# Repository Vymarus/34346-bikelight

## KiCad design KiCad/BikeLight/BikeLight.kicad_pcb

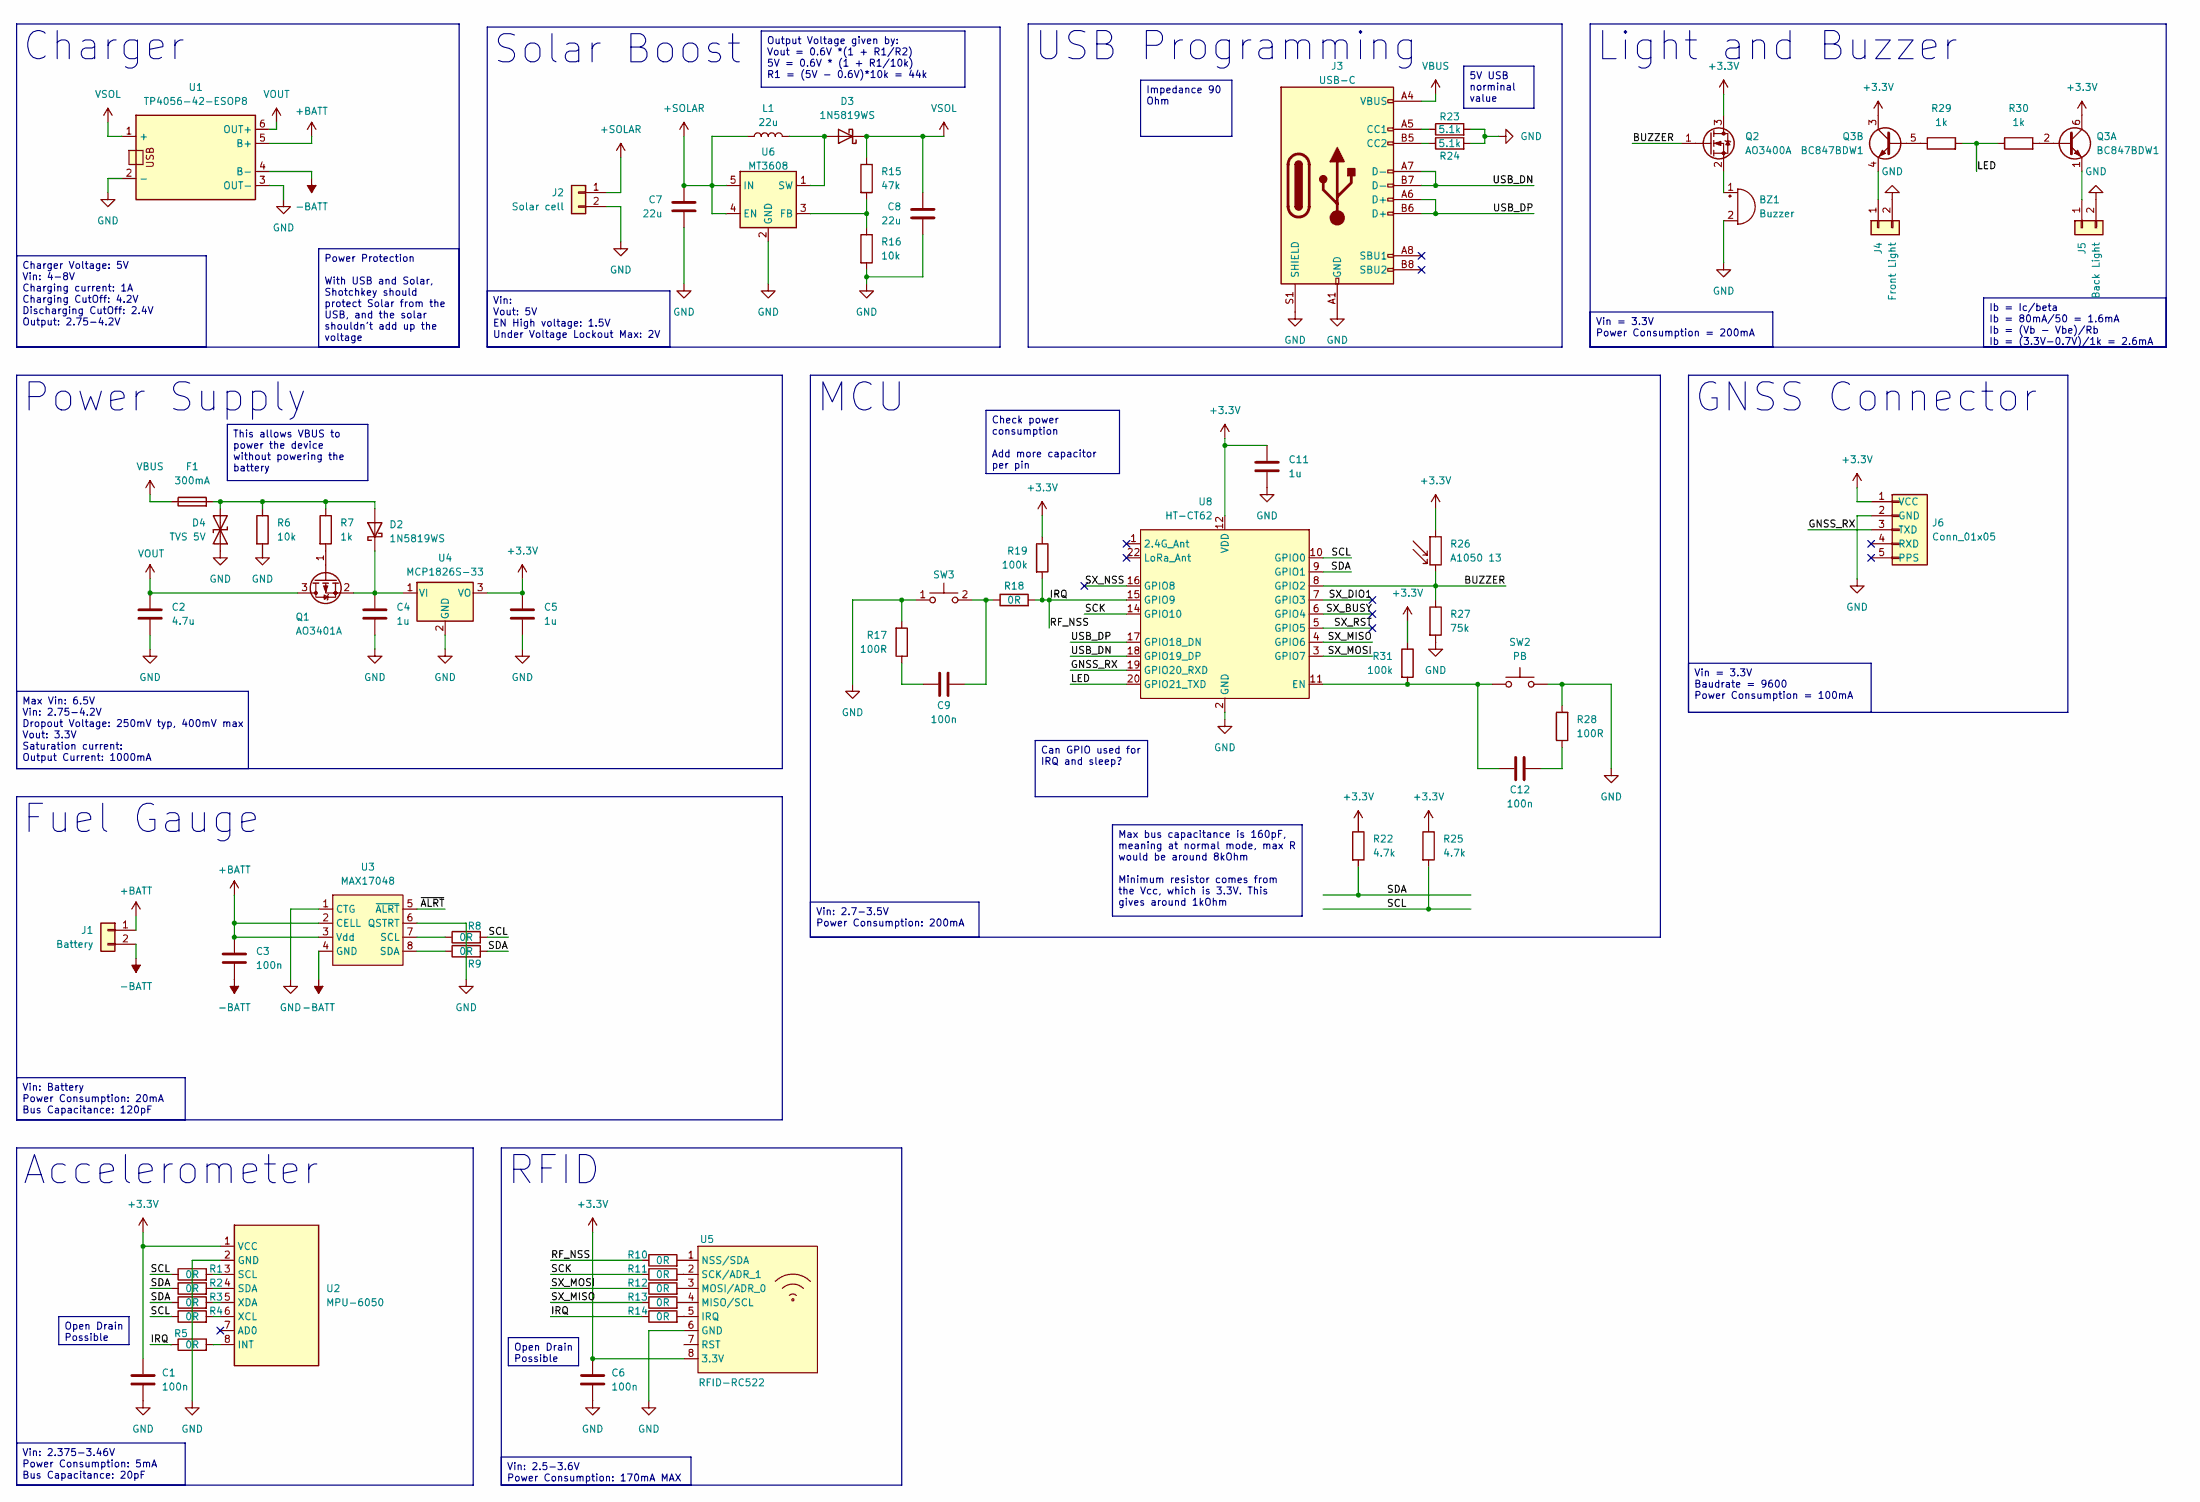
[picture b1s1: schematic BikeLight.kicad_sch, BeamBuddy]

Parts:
BZ1: TMB12A03; Buzzer_12x9.5RM7.6; MPN TMB12A03
C1, C3, C6, C9, C12: 100n_0603_TCC0603X7R104K500CT; C_0603_1608Metric; Tolerance 10%; Rating 50V; MPN TCC0603X7R104K500CT
C2: 4.7u_0805_CL21A475KAQNNNE; C_0805_2012Metric; Rating 25V; Tolerance 10%; MPN CL21A475KAQNNNE
C4: 1u_0603_CL10A105KA8NNNC; C_0603_1608Metric; MPN CL10A105KA8NNNC
C5, C11: 1u_0603_UMK107BJ105KA-T; C_0603_1608Metric; MPN UMK107BJ105KA-T
C7, C8: 22u_0805_CL21A226MAQNNNE; C_0805_2012Metric; Rating 10V; Tolerance 20%; MPN CL21A226MAQNNNE
D2, D3: 1N5819WS; D_SOD-323; MPN 1N5819WS
D4: SMAJ5.0CA/TR13_NONAME; D_SMA; MPN SMAJ5.0CA/TR13
F1: MF-MSMF010-2; Fuse_1812_4532Metric; MPN MF-MSMF010-2
J1, J2, J4, J5: Conn-01x02_P2.5mm_S2B-XH-A-BK(LF)(SN); JST_XH_S2B-XH-A_1x02_P2.50mm_Horizontal; MPN S2B-XH-A-BK(LF)(SN)
J3: GT-USB-7051A; USB-C-SMD_GT-USB-7051A; MPN GT-USB-7051A
J6: Conn_01x05; PinHeader_1x05_P2.54mm_Horizontal; LCSC C492413
L1: 22u_620mA_1210_CBC3225T220KR; L_1210_3225Metric; Rating 620mA; MPN CBC3225T220KR
Q1: AO3401A; SOT-23; MPN AO3401A
Q2: AO3400A; SOT-23; MPN AO3400A
Q3: BC847BDW1; SOT-363_SC-70-6
R1, R2, R3, R4, R5, R8, R9, R10, R11, R12, R13, R14, R18: 0R_0603_0603WAF0000T5E; R_0603_1608Metric; MPN 0603WAF0000T5E
R6, R16: 10k_0603_RC0603JR-0710KL; R_0603_1608Metric; Tolerance 1%; MPN RC0603JR-0710KL
R7, R29, R30: 1k_0603_RMC06031K1%N; R_0603_1608Metric; Tolerance 1%; MPN RMC06031K1%N
R15: 47k_0402_0402WGF1002TCE; R_0603_1608Metric; Tolerance 1%; MPN 0402WGF4702TCE
R17, R28: 100R_0603_RC0603FR-07100RL; R_0603_1608Metric; Tolerance 1%; MPN RC0603FR-07100RL
R19, R31: 100k_0603_RC0603FR-07100KL; R_0603_1608Metric; MPN RC0603FR-07100KL
R22, R25: 4.7k_0402_0402WGF4701TCE; R_0603_1608Metric; Tolerance 1%; MPN 0402WGF4701TCE
R23, R24: 5.1k_0603_0603WAF5101T5E; R_0603_1608Metric; Tolerance 1%; MPN 0603WAF5101T5E
R26: A1050 13; R_LDR_D6.4mm_P3.4mm_Vertical
R27: 75k_0603_RC0603FR-0775KL; R_0603_1608Metric; MPN RC0603FR-0775KL
SW2: SW_PB_B3F-4055; MPN B3F-4055
SW3: K2-1102AQ-H4CW-01; SW_Tactile_SPST_Angled_K2-1102AQ-H4CW-01; MPN K2-1102AQ-H4CW-01
U1: TP4056-42-ESOP8; TP4056-18650
U2: MPU-6050; GY-521_Angled
U3: MAX17048; SON50P200X200X80-9N
U4: MCP1826S-33; SOT-223-3_TabPin2
U5: RFID-RC522; RFID_RC522
U6: MT3608; SOT-23-6
U8: HT-CT62; Heltec_HT-CT62

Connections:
+3.3V: C1.1, C5.1, C6.1, C11.1, J6.1 (VCC), Q2.3 (D), Q3.3 (C2), Q3.6 (C1), R19.1, R22.1, R25.1, R26.1, R31.1, U2.1 (VCC), U4.3 (VO), U5.8 (3.3V), U8.12 (VDD)
+BATT: C3.1, J1.1, U1.5 (B+), U3.2 (CELL), U3.3 (Vdd)
+SOLAR: C7.1, J2.1, L1.1, U6.4 (EN), U6.5 (IN)
-BATT: C3.2, J1.2, U1.4 (B-), U3.4 (GND)
/BUZZER: Q2.1 (G), R26.2, R27.1, U8.8 (GPIO2)
/GNSS_RX: J6.3 (TXD), U8.19 (GPIO20_RXD)
/IRQ: R5.1, R10.1, R14.1, R18.2, R19.2, U8.15 (GPIO9)
/LED: R29.2, R30.1, U8.20 (GPIO21_TXD)
/SCK: R11.1, U8.14 (GPIO10)
/SCL: R1.1, R4.1, R8.2, R25.2, U8.10 (GPIO0)
/SDA: R2.1, R3.1, R9.2, R22.2, U8.9 (GPIO1)
/SX_BUSY: U8.6 (GPIO4)
/SX_DIO1: U8.7 (GPIO3)
/SX_MISO: R13.1, U8.4 (GPIO6)
/SX_MOSI: R12.1, U8.3 (GPIO7)
/SX_NSS: U8.16 (GPIO8)
/SX_RST: U8.5 (GPIO5)
/USB_DN: J3.A7 (D-), J3.B7 (D-), U8.18 (GPIO19_DP)
/USB_DP: J3.A6 (D+), J3.B6 (D+), U8.17 (GPIO18_DN)
/~ALRT: U3.5 (~ALRT)
GND: BZ1.2 (-), C1.2, C2.2, C4.2, C5.2, C6.2, C7.2, C8.2, C11.2, D4.1 (A1), J2.2, J3.A1 (GND), J3.A12 (GND), J3.B1 (GND), J3.B12 (GND), J3.S1 (SHIELD), J4.2, J5.2, J6.2 (GND), R6.2, R16.2, R17.2, R23.2, R24.2, R27.2, R28.2, SW2.2, SW3.1, U1.2 (-), U1.3 (OUT-), U2.2 (GND), U3.1 (CTG), U3.6 (QSTRT), U4.2 (GND), U5.6 (GND), U6.2 (GND), U8.2 (GND), U8.13 (GND), U8.21 (GND)
unnamed: BZ1.1 (+), Q2.2 (S)
unnamed: C9.1, R17.1
unnamed: C9.2, R18.1, SW3.2
unnamed: C12.1, R28.1
unnamed: D2.2 (A), D4.2 (A2), F1.2, R6.1, R7.1
unnamed: C4.1, D2.1 (K), Q1.2 (S), U4.1 (VI)
unnamed: D3.2 (A), L1.2, U6.1 (SW)
unnamed: J3.A5 (CC1), R23.1
unnamed: J3.B5 (CC2), R24.1
unnamed: J4.1, Q3.4 (E2)
unnamed: J5.1, Q3.1 (E1)
unnamed: Q1.1 (G), R7.2
unnamed: Q3.2 (B1), R30.2
unnamed: Q3.5 (B2), R29.1
unnamed: R5.2, U2.8 (INT)
unnamed: R1.2, U2.3 (SCL)
unnamed: R2.2, U2.4 (SDA)
unnamed: R4.2, U2.6 (XCL)
unnamed: R3.2, U2.5 (XDA)
unnamed: R8.1, U3.7 (SCL)
unnamed: R9.1, U3.8 (SDA)
unnamed: R14.2, U5.5 (IRQ)
unnamed: R13.2, U5.4 (MISO/SCL)
unnamed: R12.2, U5.3 (MOSI/ADR_0)
unnamed: R10.2, U5.1 (NSS/SDA)
unnamed: R11.2, U5.2 (SCK/ADR_1)
unnamed: R15.2, R16.1, U6.3 (FB)
unnamed: C12.2, R31.2, SW2.1, U8.11 (EN)
VBUS: F1.1, J3.A4 (VBUS), J3.A9 (VBUS), J3.B4 (VBUS), J3.B9 (VBUS)
VOUT: C2.1, Q1.3 (D), U1.6 (OUT+)
VSOL: C8.1, D3.1 (K), R15.1, U1.1 (+)

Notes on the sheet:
Charger
Vin: 2.5-3.6V Power Consumption: 170mA MAX
Vin: Battery Power Consumption: 20mA Bus Capacitance: 120pF
Open Drain Possible
Vin = 3.3V Baudrate = 9600 Power Consumption = 100mA
Power Supply
Vin: Vout: 5V EN High voltage: 1.5V Under Voltage Lockout Max: 2V
Output Voltage given by: Vout = 0.6V *(1 + R1/R2) 5V = 0.6V * (1 + R1/10k) R1 = (5V - 0.6V)*10k = 44k
GNSS Connector
This allows VBUS to power the device without powering the battery
Ib = Ic/beta Ib = 80mA/50 = 1.6mA Ib = (Vb - Vbe)/Rb Ib = (3.3V-0.7V)/1k = 2.6mA
USB Programming
Impedance 90 Ohm
MCU
Power Protection With USB and Solar, Shotchkey should protect Solar from the USB, and the solar shouldn't add up the voltage
5V USB norminal value
Light and Buzzer
Max Vin: 6.5V Vin: 2.75-4.2V Dropout Voltage: 250mV typ, 400mV max Vout: 3.3V Saturation current: Output Current: 1000mA
Vin: 2.7-3.5V Power Consumption: 200mA
Check power consumption Add more capacitor per pin
Vin = 3.3V Power Consumption = 200mA
Solar Boost
Can GPIO used for IRQ and sleep?
Vin: 2.375-3.46V Power Consumption: 5mA Bus Capacitance: 20pF
RFID
Charger Voltage: 5V Vin: 4-8V Charging current: 1A Charging CutOff: 4.2V Discharging CutOff: 2.4V Output: 2.75-4.2V
Max bus capacitance is 160pF, meaning at normal mode, max R would be around 8kOhm Minimum resistor comes from the Vcc, which is 3.3V. This gives around 1kOhm
Accelerometer
Fuel Gauge

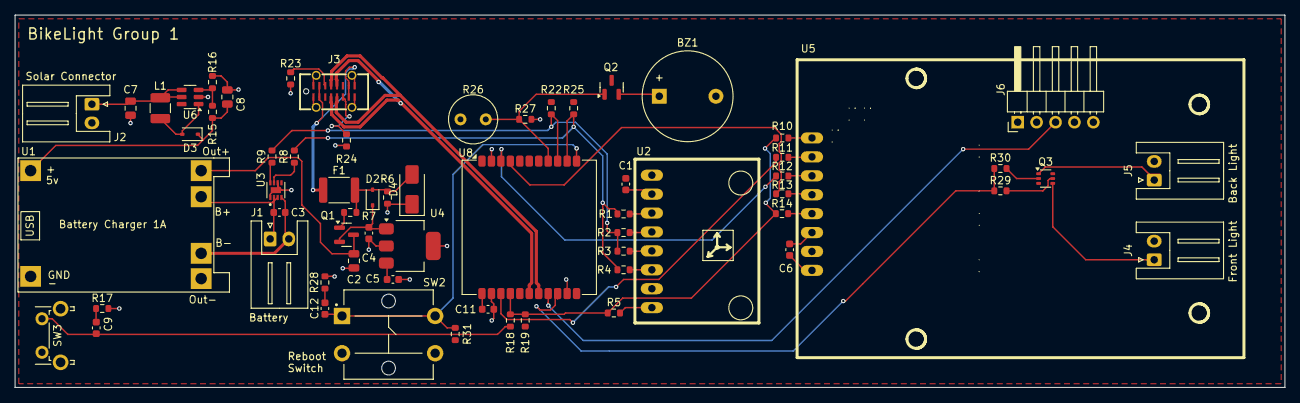
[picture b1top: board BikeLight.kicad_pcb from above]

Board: 2 copper layers, 170.5 x 50.0 mm, 64 parts (0 on the bottom side), 47 nets.

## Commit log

2025-04-21 KiCad Project and Accelerometer class
2025-04-23 Updated schematic, added datasheet
2025-04-23 Added additional datasheet
2025-04-24 started with pcb
2025-04-24 More Schematic
2025-04-25 Small adjustments to the RFID
2025-04-25 Changed RFID to use I2C
2025-04-28 Added power protection, annotated
2025-04-30 Finished most of the PCB
2025-05-01 Added Busser and LED controller
2025-05-08 Comenting files
2025-05-08 Changing GPIO pins
2025-05-14 Gerber generation
2025-05-21 Changing pins
2025-05-23 Small updates to pins
2025-05-23 Changed and updated 3D models of devices
2025-05-23 changed sheet size
2025-05-23 Cleanup and created new fabrication files
2025-05-24 Updating sch and pcb
